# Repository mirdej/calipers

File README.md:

# Calipers

Bluetooth extension for cheap digital calipers.
An ESP32 reads data from the caliper serial port and "types" it as a BLE keyboard directly into the host computer.

## Arduino Library
The caliper-reading functions have been condensed into a simple class *Calipers* inside the file **Calipers.h**.
You can use the library as a standalone library for any Arduino (not only ESP32). 

[firmware/lib/Calipers](https://github.com/mirdej/calipers/tree/main/firmware/lib/Calipers) 

There are different scales and calipers out there with different protocols. See the readme of the library for more information.

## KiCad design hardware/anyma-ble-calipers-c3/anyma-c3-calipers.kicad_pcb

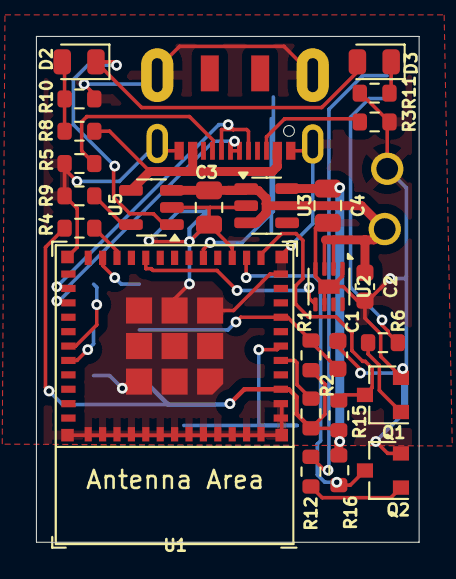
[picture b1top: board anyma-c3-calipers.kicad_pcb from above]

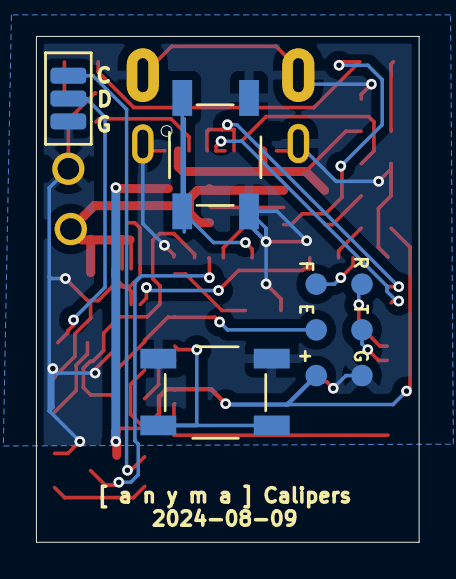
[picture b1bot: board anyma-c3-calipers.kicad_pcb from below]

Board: 2 copper layers, 21.3 x 28.1 mm, 32 parts (4 on the bottom side), 27 nets.

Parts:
C1: 1u; C_0603_1608Metric
C2: 100n; C_0603_1608Metric
C3: 10u; C_0805_2012Metric
C4: 4u7; C_0805_2012Metric
D2: CHRG; LED_0805_2012Metric
D3: RDY; LED_0805_2012Metric
J1: Conn_01x03_Pin; solderpad_1.27mm_3
J2: Prog; AnymaPOGO-ESP
J3: USB_C_Receptacle_USB2.0; JAE_USB-C_SJ122205
J9: BATT+; Solderpad_1mm
J10: BATT-; Solderpad_1mm
Q1, Q2: BC847; SOT-23_BEC
R1, R2, R3, R4, R5: 5k1; R_0603_1608Metric
R6, R12: 560; R_0603_1608Metric
R8, R9, R10, R11: 2k; R_0603_1608Metric
R15, R16: 51k; R_0603_1608Metric
SW2: Btn-1; Alps_Tactile_Switch
SW4: Btn-2; Alps_Tactile_Switch
U1: ESP32-C3-MINI-1
U2: TDFN-8-1EP_2x2mm_P0.5mm_EP0.8x1.2mm
U3: XC6220B331MR; SOT-23-5
U5: MCP73831-2-OT; SOT-23-5

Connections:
+3V3: C4.1, J2.1, R1.1, R2.1, R4.1, R15.2, R16.2, U1.3 (3V3), U3.5 (VOUT)
+5V: J3.A4 (VBUS), J3.A9 (VBUS), R8.1, U5.4 (VDD)
+BATT: C2.1, C3.1, J9.1, U2.2 (CELL), U2.3 (VDD), U3.1 (VIN), U3.3 (CE), U5.3 (VBAT)
/clock: J1.1, R12.1
/data: J1.2, R6.1
/en: C1.1, J2.2, R1.2, U1.8 (EN/CHIP_PU)
/flash: J2.3, U1.23 (GPIO9)
/gpio_0: Q1.C, R15.1, U1.12 (GPIO0/ADC1_CH0/XTAL_32K_P)
/gpio_1: Q2.C, R16.1, U1.13 (GPIO1/ADC1_CH1/XTAL_32K_N)
/gpio_6: U1.20 (GPIO6), U2.5 (!ALRT)
/rx: J2.4, U1.30 (GPIO20/U0RXD)
/strap1: R4.2, U1.22 (GPIO8)
/strap2: R2.2, U1.5 (GPIO2/ADC1_CH2)
/tx: J2.5, U1.31 (GPIO21/U0TXD)
/usb+: J3.A6 (D+), J3.B6 (D+), U1.27 (GPIO19/USB_D+)
/usb-: J3.A7 (D-), J3.B7 (D-), U1.26 (GPIO18/USB_D-)
GND: C1.2, C2.2, C3.2, C4.2, J1.3, J2.6, J3.A1 (GND), J3.A12 (GND), J3.S1 (SHIELD), J10.1, Q1.E, Q2.E, R3.2, R5.2, R9.2, R10.2, R11.2, SW2.2, SW4.2, U1.1 (GND), U1.2 (GND), U1.11 (GND), U1.14 (GND), U1.36 (GND), U1.37 (GND), U1.38 (GND), U1.39 (GND), U1.40 (GND), U1.41 (GND), U1.42 (GND), U1.43 (GND), U1.44 (GND), U1.45 (GND), U1.46 (GND), U1.47 (GND), U1.48 (GND), U1.49 (GND), U1.50 (GND), U1.51 (GND), U1.52 (GND), U1.53 (GND), U2.1 (CTG), U2.4 (GND), U2.6 (QSTRT), U2.9 (EP), U3.2 (GND), U5.2 (VSS)
unnamed: D2.2 (A), R8.2, R10.1
unnamed: D2.1 (K), D3.2 (A), U5.1 (STAT)
unnamed: D3.1 (K), R11.1
unnamed: J3.A5 (CC1), R3.1
unnamed: J3.B5 (CC2), R5.1
unnamed: Q1.B, R6.2
unnamed: Q2.B, R12.2
unnamed: SW4.1, U1.6 (GPIO3/ADC1_CH3)
unnamed: SW2.1, U1.16 (GPIO10)
unnamed: R9.1, U5.5 (PROG)

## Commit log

2024-07-31 more on isr in classes
2024-07-31 compiles for other arduinos as well, not only esp32
2024-07-31 lint
2024-07-31 add example sketch
2024-07-31 fix negative numbers
2024-07-31 add link to library
2024-07-31 add pcb
2024-08-30 china hardware version
